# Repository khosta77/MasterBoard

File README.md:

# Мастер плата для управления ЧПУ станком

Развиваю плату.

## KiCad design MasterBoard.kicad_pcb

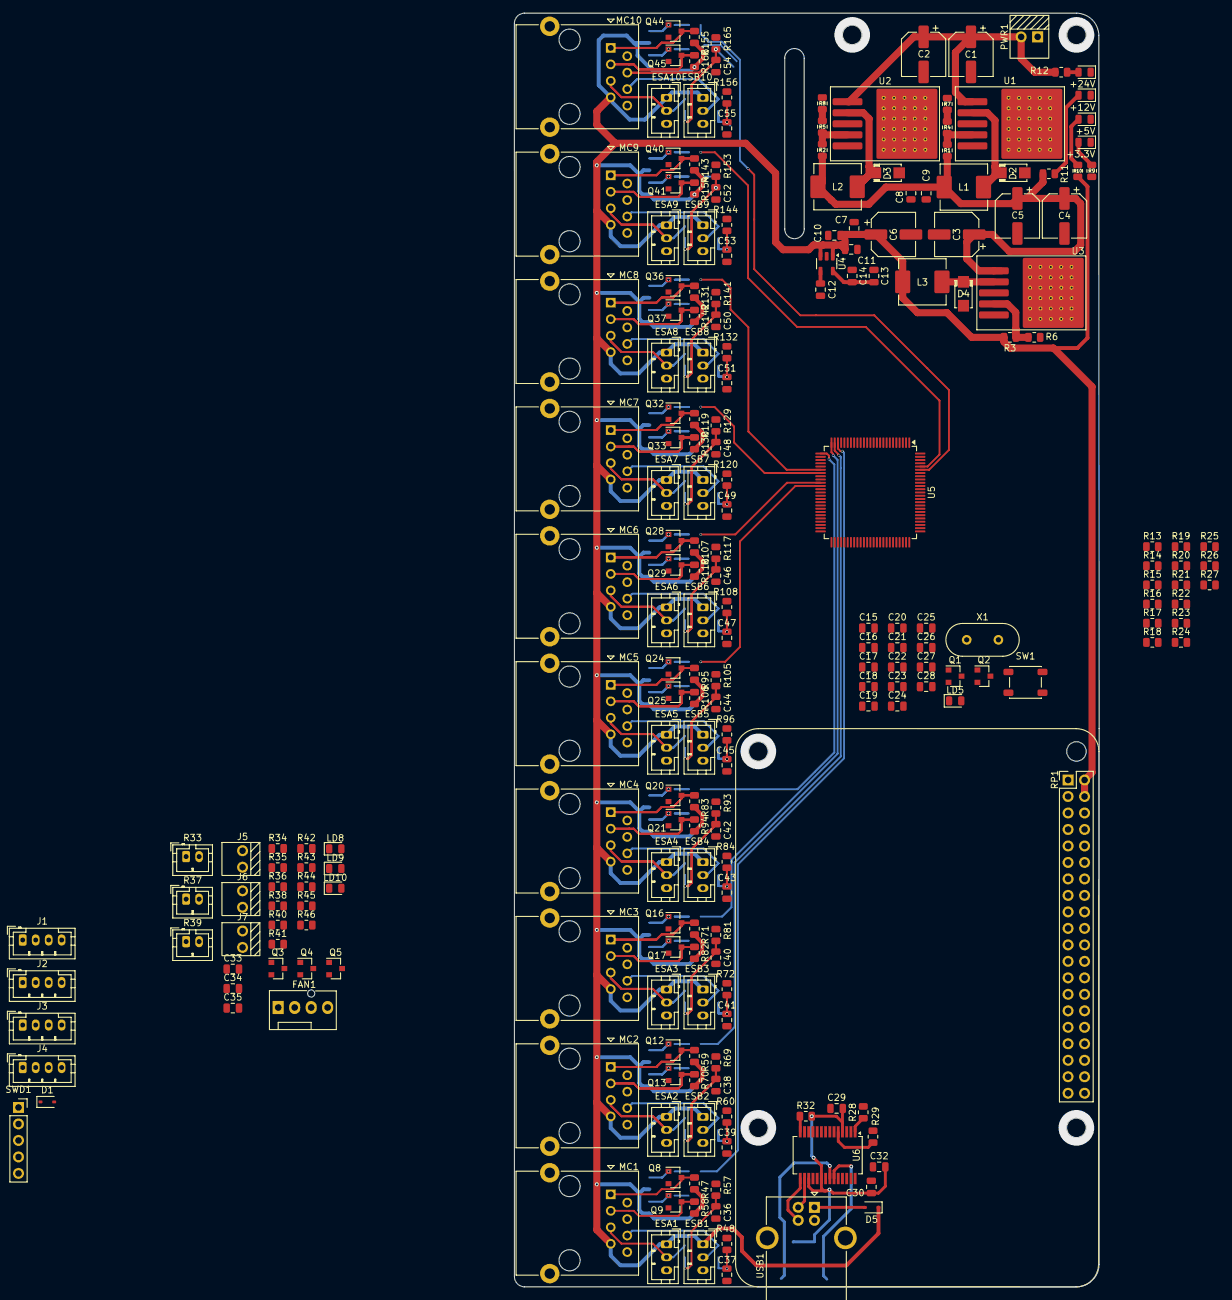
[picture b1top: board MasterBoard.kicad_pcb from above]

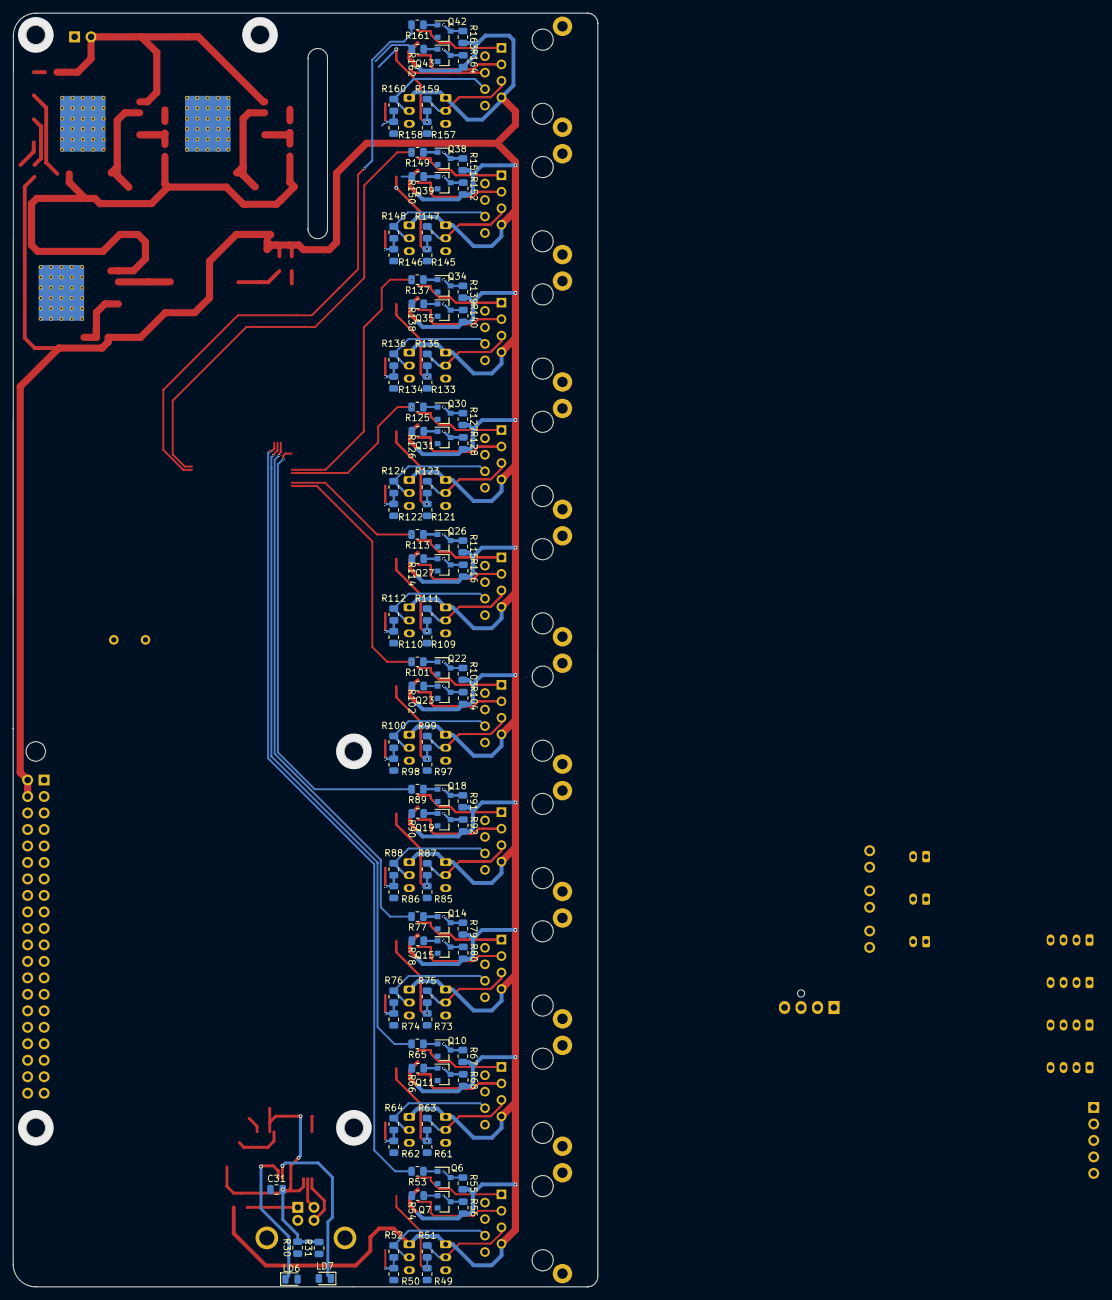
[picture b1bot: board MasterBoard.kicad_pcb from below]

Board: 2 copper layers, 90.1 x 196.2 mm, 334 parts (105 on the bottom side), 200 nets.

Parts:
C1, C2, C3: 100u; CP_Elec_6.3x7.7
C4, C5, C6: 220u; CP_Elec_6.3x7.7
C7, C8, C9: 10n; C_0805_2012Metric
C10: 1u; C_0805_2012Metric
C11, C14, C15, C18, C19, C20, C23, C24, C25, C26, C27, C30, C32, C33, C34, C35, C36, C37, C38, C39, C40, C41, C42, C43, C44, C45, C46, C47, C48, C49, C50, C51, C52, C53, C54, C55: 100n; C_0805_2012Metric
C12: 22n; C_0805_2012Metric
C13, C29: 10u; C_0805_2012Metric
C16, C17: 2.2u; C_0805_2012Metric
C21, C22: 20p; C_0805_2012Metric
C28, C31: 4.7u; C_0805_2012Metric
D1, D5: BAT60A; D_SOD-323
D2, D3, D4: 1N5822; D_DO-214AC_SMA
ESA1, ESA2, ESA3, ESA4, ESA5, ESA6, ESA7, ESA8, ESA9, ESA10: ESA; JST_PH_B3B-PH-K_1x03_P2.00mm_Vertical
ESB1, ESB2, ESB3, ESB4, ESB5, ESB6, ESB7, ESB8, ESB9, ESB10: ESB; JST_PH_B3B-PH-K_1x03_P2.00mm_Vertical
FAN1: Fan_CPU_4pin; FanPinHeader_1x04_P2.54mm_Vertical
J1, J2, J3, J4: HX711; JST_PH_B4B-PH-K_1x04_P2.00mm_Vertical
J5, J6, J7: WF-2
L1, L2, L3: 33u; L_APV_APH0650
LD1, LD2, LD3, LD4, LD5, LD6, LD7, LD8, LD9, LD10: LED_0805_2012Metric
MC1, MC2, MC3, MC4, MC5, MC6, MC7, MC8, MC9, MC10: RJ45_Shielded; RJ45_Ninigi_GE
PWR1: Conn_01x02; KLS2
Q1, Q2, Q6, Q7, Q8, Q9, Q10, Q11, Q12, Q13, Q14, Q15, Q16, Q17, Q18, Q19, Q20, Q21, Q22, Q23, Q24, Q25, Q26, Q27, Q28, Q29, Q30, Q31, Q32, Q33, Q34, Q35, Q36, Q37, Q38, Q39, Q40, Q41, Q42, Q43, Q44, Q45: MMBT3904; SOT-23
Q3, Q4, Q5: 2N7002; SOT-23
R1, R2: 1.2k; R_0805_2012Metric
R3: 3k; R_0805_2012Metric
R4, R5: 500; R_0805_2012Metric
R6, R9, R10, R11, R12, R24, R28, R29, R30, R31, R42, R44, R46: 1k; R_0805_2012Metric
R7, R8, R13, R16, R25, R26, R27, R32, R34, R38, R40, R41, R43, R45, R47, R48, R51, R52, R53, R54, R55, R56, R57, R58, R59, R60, R63, R64, R65, R66, R67, R68, R69, R70, R71, R72, R75, R76, R77, R78, R79, R80, R81, R82, R83, R84, R87, R88, R89, R90, R91, R92, R93, R94, R95, R96, R99, R100, R101, R102, R103, R104, R105, R106, R107, R108, R111, R112, R113, R114, R115, R116, R117, R118, R119, R120, R123, R124, R125, R126, R127, R128, R129, R130, R131, R132, R135, R136, R137, R138, R139, R140, R141, R142, R143, R144, R147, R148, R149, R150, R151, R152, R153, R154, R155, R156, R159, R160, R161, R162, R163, R164, R165, R166: 10k; R_0805_2012Metric
R14, R15, R17, R18, R19, R20, R21, R22, R23: 10; R_0805_2012Metric
R33, R37, R39: 10k; JST_PH_B2B-PH-K_1x02_P2.00mm_Vertical
R35, R36: -; R_0805_2012Metric
R49, R50, R61, R62, R73, R74, R85, R86, R97, R98, R109, R110, R121, R122, R133, R134, R145, R146, R157, R158: 15k; R_0805_2012Metric
RP1: Raspberry_Pi_2_3; PinHeader_2x20_P2.54mm_Vertical
SW1: SW_DPST_x2; SW_SPST_PTS647_Sx38
SWD1: Conn_01x05_Socket; PinSocket_1x05_P2.54mm_Vertical
U1, U2, U3: LM2596S-ADJ; TO-263-5_TabPin3_ThermalVias
U4: RT9193-33GB; SOT-23-5
U5: STM32F407VGTx; LQFP-100_14x14mm_P0.5mm
U6: FT232RL; SSOP-28_5.3x10.2mm_P0.65mm
USB1: USB_B; USB_B_OST_USB-B1HSxx_Horizontal
X1: 8MHz; Crystal_HC49-U_Vertical

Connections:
+3.3V: C13.2, C14.2, C18.1, C19.1, C20.1, C23.1, C24.1, C25.1, C26.1, C27.1, C28.1, C29.2, C30.2, C31.2, C32.2, C33.1, C34.1, C35.1, D1.1 (K), R9.1, R13.2, R24.2, R30.2, R31.2, R32.2, R33.1, R37.1, R39.1, R47.2, R48.2, R59.2, R60.2, R71.2, R72.2, R83.2, R84.2, R95.2, R96.2, R107.2, R108.2, R119.2, R120.2, R131.2, R132.2, R143.2, R144.2, R155.2, R156.2, RP1.1 (3V3), RP1.17 (3V3), SW1.2 (B), U4.5 (VOUT), U5.6 (VBAT), U5.11 (VDD), U5.19 (VDD), U5.21 (VREF+), U5.22 (VDDA), U5.28 (VDD), U5.50 (VDD), U5.75 (VDD), U5.100 (VDD), U6.4 (VCCIO), U6.17 (3V3OUT), U6.20 (VCC)
+5V: C6.1, C7.2, C10.2, C11.2, D5.1 (K), ESA1.1, ESA2.1, ESA3.1, ESA4.1, ESA5.1, ESA6.1, ESA7.1, ESA8.1, ESA9.1, ESA10.1, ESB1.1, ESB2.1, ESB3.1, ESB4.1, ESB5.1, ESB6.1, ESB7.1, ESB8.1, ESB9.1, ESB10.1, J1.1, J2.1, J3.1, J4.1, J5.1, J6.1, J7.1, L3.2, MC1.7, MC2.7, MC3.7, MC4.7, MC5.7, MC6.7, MC7.7, MC8.7, MC9.7, MC10.7, R3.2, R10.1, R26.2, R27.2, R55.2, R56.2, R57.2, R58.2, R67.2, R68.2, R69.2, R70.2, R79.2, R80.2, R81.2, R82.2, R91.2, R92.2, R93.2, R94.2, R103.2, R104.2, R105.2, R106.2, R115.2, R116.2, R117.2, R118.2, R127.2, R128.2, R129.2, R130.2, R139.2, R140.2, R141.2, R142.2, R151.2, R152.2, R153.2, R154.2, R163.2, R164.2, R165.2, R166.2, RP1.2 (5V), RP1.4 (5V), U4.1 (VIN), U4.3 (EN)
+12V: C3.1, C4.1, C5.1, C8.2, C9.2, FAN1.2 (+), L1.2, L2.2, R1.2, R2.2, R11.1, U3.1 (VIN)
+24V: C1.1, C2.1, PWR1.2, R12.1, U1.1 (VIN), U2.1 (VIN)
/ADC12_IN4: C33.2, R33.2, R34.1, U5.29 (PA4)
/ADC12_IN5: C34.2, R37.2, R38.1, U5.30 (PA5)
/ADC12_IN14: C35.2, R39.2, R40.1, U5.33 (PC4)
/ES_A_0: C36.1, R47.1, R49.2, R51.2
/ES_A_1: C38.1, R59.1, R61.2, R63.2
/ES_A_2: C40.1, R71.1, R73.2, R75.2
/ES_A_3: C42.1, R83.1, R85.2, R87.2
/ES_A_4: C44.1, R95.1, R97.2, R99.2
/ES_A_5: C46.1, R107.1, R109.2, R111.2
/ES_A_6: C48.1, R119.1, R121.2, R123.2
/ES_A_7: C50.1, R131.1, R133.2, R135.2
/ES_A_8: C52.1, R143.1, R145.2, R147.2
/ES_A_9: C54.1, R155.1, R157.2, R159.2
/ES_B_0: C37.1, R48.1, R50.2, R52.2
/ES_B_1: C39.1, R60.1, R62.2, R64.2
/ES_B_2: C41.1, R72.1, R74.2, R76.2
/ES_B_3: C43.1, R84.1, R86.2, R88.2
/ES_B_4: C45.1, R96.1, R98.2, R100.2
/ES_B_5: C47.1, R108.1, R110.2, R112.2
/ES_B_6: C49.1, R120.1, R122.2, R124.2
/ES_B_7: C51.1, R132.1, R134.2, R136.2
/ES_B_8: C53.1, R144.1, R146.2, R148.2
/ES_B_9: C55.1, R156.1, R158.2, R160.2
/HX711_DAT_1: J1.3, U5.82 (PD1)
/HX711_DAT_2: J2.3, U5.84 (PD3)
/HX711_DAT_3: J3.3, U5.55 (PD8)
/HX711_DAT_4: J4.3, U5.57 (PD10)
/HX711_SCK_1: J1.2, U5.81 (PD0)
/HX711_SCK_2: J2.2, U5.83 (PD2)
/HX711_SCK_3: J3.2, U5.88 (PD7)
/HX711_SCK_4: J4.2, U5.56 (PD9)
/Motor0/DIR: MC1.3, Q9.3 (C), R58.1
/Motor0/ESA: ESA1.2, MC1.5, R51.1
/Motor0/ESB: ESB1.2, MC1.6, R52.1
/Motor0/STEP: MC1.1, Q8.3 (C), R57.1
/Motor1/DIR: MC2.3, Q13.3 (C), R70.1
/Motor1/ESA: ESA2.2, MC2.5, R63.1
/Motor1/ESB: ESB2.2, MC2.6, R64.1
/Motor1/STEP: MC2.1, Q12.3 (C), R69.1
/Motor2/DIR: MC3.3, Q17.3 (C), R82.1
/Motor2/ESA: ESA3.2, MC3.5, R75.1
/Motor2/ESB: ESB3.2, MC3.6, R76.1
/Motor2/STEP: MC3.1, Q16.3 (C), R81.1
/Motor3/DIR: MC4.3, Q21.3 (C), R94.1
/Motor3/ESA: ESA4.2, MC4.5, R87.1
/Motor3/ESB: ESB4.2, MC4.6, R88.1
/Motor3/STEP: MC4.1, Q20.3 (C), R93.1
/Motor4/DIR: MC5.3, Q25.3 (C), R106.1
/Motor4/ESA: ESA5.2, MC5.5, R99.1
/Motor4/ESB: ESB5.2, MC5.6, R100.1
/Motor4/STEP: MC5.1, Q24.3 (C), R105.1
/Motor5/DIR: MC6.3, Q29.3 (C), R118.1
/Motor5/ESA: ESA6.2, MC6.5, R111.1
/Motor5/ESB: ESB6.2, MC6.6, R112.1
/Motor5/STEP: MC6.1, Q28.3 (C), R117.1
/Motor6/DIR: MC7.3, Q33.3 (C), R130.1
/Motor6/ESA: ESA7.2, MC7.5, R123.1
/Motor6/ESB: ESB7.2, MC7.6, R124.1
/Motor6/STEP: MC7.1, Q32.3 (C), R129.1
/Motor7/DIR: MC8.3, Q37.3 (C), R142.1
/Motor7/ESA: ESA8.2, MC8.5, R135.1
/Motor7/ESB: ESB8.2, MC8.6, R136.1
/Motor7/STEP: MC8.1, Q36.3 (C), R141.1
/Motor8/DIR: MC9.3, Q41.3 (C), R154.1
/Motor8/ESA: ESA9.2, MC9.5, R147.1
/Motor8/ESB: ESB9.2, MC9.6, R148.1
/Motor8/STEP: MC9.1, Q40.3 (C), R153.1
/Motor9/DIR: MC10.3, Q45.3 (C), R166.1
/Motor9/ESA: ESA10.2, MC10.5, R159.1
/Motor9/ESB: ESB10.2, MC10.6, R160.1
/Motor9/STEP: MC10.1, Q44.3 (C), R165.1
/RP_RST: C15.1, R13.1, RP1.12 (GPIO18/PWM0), SW1.1 (A), U5.14 (NRST)
/RP_UART1_RX: R14.2, RP1.28 (ID_SC/GPIO1)
/RP_UART1_TX: R15.2, RP1.27 (ID_SD/GPIO0)
/RP_UART_RX: R17.1, RP1.10 (GPIO15/RXD)
/RP_UART_TX: R18.1, RP1.8 (GPIO14/TXD)
/SOME_PIN_0: RP1.22 (GPIO25), U5.7 (PC13)
/SOME_PIN_1: RP1.37 (GPIO26), U5.8 (PC14)
/SOME_PIN_2: RP1.13 (GPIO27), U5.9 (PC15)
/SPI2_CS: R19.1, RP1.24 (~CE0/GPIO8)
/SPI2_MISO: R22.1, RP1.21 (MISO0/GPIO9)
/SPI2_MOSI: R23.1, RP1.19 (MOSI0/GPIO10)
/SPI2_NSS: R20.1, RP1.26 (~CE1/GPIO7)
/SPI2_SCK: R21.1, RP1.23 (SCLK0/GPIO11)
/STM32F407VG/OSC_IN: C21.2, U5.12 (PH0), X1.2
/STM32F407VG/OSC_OUT: C22.2, U5.13 (PH1), X1.1
/STM32F407VG/PA8: LD5.1 (K), U5.67 (PA8)
/STM32F407VG/PD4: R25.2, U5.85 (PD4)
/SWCLK: SWD1.3, U5.76 (PA14)
/SWDIO: SWD1.2, U5.72 (PA13)
/TIM2/5_STEP_1: R53.2, U5.23 (PA0)
/TIM2/5_STEP_2: R65.2, U5.24 (PA1)
/TIM2/5_STEP_3: R77.2, U5.25 (PA2)
/TIM2/5_STEP_4: R89.2, U5.26 (PA3)
/TIM3_STEP_1: R137.2, U5.31 (PA6)
/TIM3_STEP_2: R125.2, U5.32 (PA7)
/TIM3_STEP_3: R113.2, U5.35 (PB0)
/TIM3_STEP_4: R101.2, U5.36 (PB1)
/TIM4_PWM_3: Q3.1 (G), R41.2, U5.93 (PB7)
/TIM4_PWM_4: Q5.1 (G), R45.2, U5.92 (PB6)
/TIM4_STEP_1: R149.2, U5.96 (PB9)
/TIM4_STEP_2: R161.2, U5.95 (PB8)
/TIM8_2_TABLE_ON: Q4.1 (G), R43.2, U5.64 (PC7)
/TIM8_3_FAN_PWM: FAN1.4 (PWM), U5.65 (PC8)
/TIM8_4_TACHO: R35.1, R36.2, U5.66 (PC9)
EN: MC1.4, MC2.4, MC3.4, MC4.4, MC5.4, MC6.4, MC7.4, MC8.4, MC9.4, MC10.4, Q2.3 (C), R27.1
GND: C1.2, C2.2, C3.2, C4.2, C5.2, C6.2, C7.1, C8.1, C9.1, C10.1, C11.1, C12.1, C13.1, C14.1, C15.2, C16.2, C17.2, C18.2, C19.2, C20.2, C21.1, C22.1, C23.2, C24.2, C25.2, C26.2, C27.2, C28.2, C29.1, C30.1, C31.1, C32.1, C36.2, C37.2, C38.2, C39.2, C40.2, C41.2, C42.2, C43.2, C44.2, C45.2, C46.2, C47.2, C48.2, C49.2, C50.2, C51.2, C52.2, C53.2, C54.2, C55.2, D2.2 (A), D3.2 (A), D4.2 (A), ESA1.3, ESA2.3, ESA3.3, ESA4.3, ESA5.3, ESA6.3, ESA7.3, ESA8.3, ESA9.3, ESA10.3, ESB1.3, ESB2.3, ESB3.3, ESB4.3, ESB5.3, ESB6.3, ESB7.3, ESB8.3, ESB9.3, ESB10.3, FAN1.1 (-), J1.4, J2.4, J3.4, J4.4, LD1.1 (K), LD2.1 (K), LD3.1 (K), LD4.1 (K), MC1.2, MC1.8, MC1.SH, MC2.2, MC2.8, MC2.SH, MC3.2, MC3.8, MC3.SH, MC4.2, MC4.8, MC4.SH, MC5.2, MC5.8, MC5.SH, MC6.2, MC6.8, MC6.SH, MC7.2, MC7.8, MC7.SH, MC8.2, MC8.8, MC8.SH, MC9.2, MC9.8, MC9.SH, MC10.2, MC10.8, MC10.SH, PWR1.1, Q1.2 (E), Q2.2 (E), Q3.2 (S), Q4.2 (S), Q5.2 (S), Q6.2 (E), Q7.2 (E), Q8.2 (E), Q9.2 (E), Q10.2 (E), Q11.2 (E), Q12.2 (E), Q13.2 (E), Q14.2 (E), Q15.2 (E), Q16.2 (E), Q17.2 (E), Q18.2 (E), Q19.2 (E), Q20.2 (E), Q21.2 (E), Q22.2 (E), Q23.2 (E), Q24.2 (E), Q25.2 (E), Q26.2 (E), Q27.2 (E), Q28.2 (E), Q29.2 (E), Q30.2 (E), Q31.2 (E), Q32.2 (E), Q33.2 (E), Q34.2 (E), Q35.2 (E), Q36.2 (E), Q37.2 (E), Q38.2 (E), Q39.2 (E), Q40.2 (E), Q41.2 (E), Q42.2 (E), Q43.2 (E), Q44.2 (E), Q45.2 (E), R6.2, R7.2, R8.2, R16.2, R34.2, R36.1, R38.2, R40.2, R41.1, R43.1, R45.1, R49.1, R50.1, R61.1, R62.1, R73.1, R74.1, R85.1, R86.1, R97.1, R98.1, R109.1, R110.1, R121.1, R122.1, R133.1, R134.1, R145.1, R146.1, R157.1, R158.1, RP1.6 (GND), RP1.9 (GND), RP1.11 (GPIO17), RP1.14 (GND), RP1.20 (GND), RP1.25 (GND), RP1.30 (GND), RP1.34 (GND), RP1.39 (GND), SWD1.4, U1.3 (GND), U1.5 (~ON/OFF), U2.3 (GND), U2.5 (~ON/OFF), U3.3 (GND), U3.5 (~ON/OFF), U4.2 (GND), U5.10 (VSS), U5.20 (VSSA), U5.27 (VSS), U5.74 (VSS), U5.99 (VSS), U6.7 (GND), U6.18 (GND), U6.21 (GND), U6.25 (AGND), U6.26 (TEST), USB1.4 (GND), USB1.5 (Shield)
unnamed: D1.2 (A), SWD1.1
unnamed: D2.1 (K), L1.1, U1.2 (OUT)
unnamed: D3.1 (K), L2.1, U2.2 (OUT)
unnamed: D4.1 (K), L3.1, U3.2 (OUT)
unnamed: D5.2 (A), USB1.1 (VBUS)
unnamed: FAN1.3 (Tacho), R35.2
unnamed: J5.2, LD8.2 (A)
unnamed: J6.2, LD9.2 (A)
unnamed: J7.2, LD10.2 (A)
unnamed: LD1.2 (A), R9.2
unnamed: LD2.2 (A), R10.2
unnamed: LD3.2 (A), R11.2
unnamed: LD4.2 (A), R12.2
unnamed: LD5.2 (A), R24.1
unnamed: LD6.2 (A), R30.1
unnamed: LD6.1 (K), U6.23 (CBUS0)
unnamed: LD7.2 (A), R31.1
unnamed: LD7.1 (K), U6.22 (CBUS1)
unnamed: LD8.1 (K), R42.1
unnamed: LD9.1 (K), R44.1
unnamed: LD10.1 (K), R46.1
unnamed: Q1.1 (B), R25.1
unnamed: Q1.3 (C), Q2.1 (B), R26.1
unnamed: Q3.3 (D), R42.2
unnamed: Q4.3 (D), R44.2
unnamed: Q5.3 (D), R46.2
unnamed: Q6.1 (B), R53.1
unnamed: Q6.3 (C), Q8.1 (B), R55.1
unnamed: Q7.1 (B), R54.1
unnamed: Q7.3 (C), Q9.1 (B), R56.1
unnamed: Q10.1 (B), R65.1
unnamed: Q10.3 (C), Q12.1 (B), R67.1
unnamed: Q11.1 (B), R66.1
unnamed: Q11.3 (C), Q13.1 (B), R68.1
unnamed: Q14.1 (B), R77.1
unnamed: Q14.3 (C), Q16.1 (B), R79.1
unnamed: Q15.1 (B), R78.1
unnamed: Q15.3 (C), Q17.1 (B), R80.1
unnamed: Q18.1 (B), R89.1
unnamed: Q18.3 (C), Q20.1 (B), R91.1
unnamed: Q19.1 (B), R90.1
unnamed: Q19.3 (C), Q21.1 (B), R92.1
unnamed: Q22.1 (B), R101.1
unnamed: Q22.3 (C), Q24.1 (B), R103.1
unnamed: Q23.1 (B), R102.1
unnamed: Q23.3 (C), Q25.1 (B), R104.1
unnamed: Q26.1 (B), R113.1
unnamed: Q26.3 (C), Q28.1 (B), R115.1
unnamed: Q27.1 (B), R114.1
unnamed: Q27.3 (C), Q29.1 (B), R116.1
unnamed: Q30.1 (B), R125.1
unnamed: Q30.3 (C), Q32.1 (B), R127.1
unnamed: Q31.1 (B), R126.1
unnamed: Q31.3 (C), Q33.1 (B), R128.1
unnamed: Q34.1 (B), R137.1
unnamed: Q34.3 (C), Q36.1 (B), R139.1
unnamed: Q35.1 (B), R138.1
unnamed: Q35.3 (C), Q37.1 (B), R140.1
unnamed: Q38.1 (B), R149.1
unnamed: Q38.3 (C), Q40.1 (B), R151.1
unnamed: Q39.1 (B), R150.1
unnamed: Q39.3 (C), Q41.1 (B), R152.1
unnamed: Q42.1 (B), R161.1
unnamed: Q42.3 (C), Q44.1 (B), R163.1
unnamed: Q43.1 (B), R162.1
unnamed: Q43.3 (C), Q45.1 (B), R164.1
unnamed: R4.2, R7.1
unnamed: R5.2, R8.1
unnamed: R1.1, R4.1, U1.4 (FB)
unnamed: R2.1, R5.1, U2.4 (FB)
unnamed: R3.1, R6.1, U3.4 (FB)
unnamed: C12.2, U4.4 (BP)
unnamed: R16.1, U5.94 (BOOT0)
unnamed: R17.2, U5.68 (PA9)
unnamed: R18.2, U5.69 (PA10)
unnamed: R19.2, U5.48 (PB11)
unnamed: R20.2, U5.51 (PB12)
unnamed: R21.2, U5.52 (PB13)
unnamed: R22.2, U5.53 (PB14)
unnamed: R23.2, U5.54 (PB15)
unnamed: R14.1, U5.86 (PD5)
unnamed: R15.1, U5.87 (PD6)
unnamed: C16.1, U5.49 (VCAP_1)
unnamed: C17.1, U5.73 (VCAP_2)
unnamed: R32.1, U6.14 (CBUS3)
unnamed: R29.1, U6.5 (RXD)
unnamed: R28.1, U6.1 (TXD)
unnamed: U6.15 (USBD+), USB1.3 (D+)
unnamed: U6.16 (USBD-), USB1.2 (D-)

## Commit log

2025-02-22 Искл файлы
2025-02-22 Файлы проекта
2025-02-22 Схемы stm32f4, stlink финальные, в power еще что нибудь добавлю. Остальные пока не подключены
2025-02-24 Еще одно искл
2025-02-24 Обновил файлы и добавил новые элемнты
2025-02-24 Внутренние изменения
2025-02-25 Новые схемы, множество
2025-02-25 Добавил много схем, близок к тому чтобы общий вид платы доделать
2025-02-27 Добавил концевик в схему и подправил схему мотора
2025-02-27 Добавил движки, концевики, и шлейфы
2025-02-27 Модуль W5500
2025-02-27 Добавил модуль W5500. Посчитал амбиции платы, не хватает пинов в МК, решил удалить(убрать из симуляции) концевики дополнительные
2025-03-01 Что-то поменялось
2025-03-01 Добавил еще один интернет модуль
2025-03-01 Добавил карту памяти
2025-03-01 Поменял микроконтроллер на поменьше
2025-03-01 Файлы измененный Kicad
2025-03-01 Начал править нумерацию элементов, и устанавливать посадочные места
2025-03-01 Прошелся по всей схеме: 1. почистил компоненты; 2. задал посадочные места; 3. Выставил все ссылки на плате в притык, дальнейшее расширение - смена мк
2025-03-01 Часть с схемой платы в кокойто степени дошла до этапа дебага
2025-03-01 Хмм в библиотеки был косяк
2025-03-01 Выгрузил элементы в трассировщик, модели все подгружены, настал этап трассировки платы
2025-03-04 Не корректно посадочное место выбрал
2025-03-04 Радикальное рубилово частей схемы
2025-03-04 Решил отказатся от платы Ender
2025-03-05 Перенс файлы что надо бы сохранить на всякий в отдельную директорию
2025-03-05 Множественные модификации
2025-03-05 Обновил плату, убрал много элементов. посчитал, что так будет лучше
2025-03-06 Надо будет сохранить
2025-03-06 Сохранил буфер
2025-03-06 Добавил описание и лицензию
2025-03-12 Был косяк в обозначениях
2025-03-12 Начал делать трассировку
2025-03-12 Новое исключение
2025-03-14 Изменил на подключение промышленного мотора
2025-03-14 Удалил TMP100 - лишний груз был
2025-03-14 Обновил/почистил схему
2025-03-14 Мелкие перестановки, просто кое что прикидывал
2025-03-14 Вернул старый добрый микроконтроллер
2025-03-14 Вынес перефирию в отдельный блок, в данный момент так разумнее
2025-03-14 Предфинальный облик мотора, нужно еще добавить пару моментов
2025-03-14 Множественная перекомпоновка
2025-03-14 Системные измененния
2025-03-14 Удалил уже не используемые файлы
2025-03-14 Добавил разъемы, для концевиков
2025-03-14 Добавил кнопку на сброс
2025-03-14 Вывел все выводы, но еще не соединил
2025-03-14 Выписал из схемы какого то препода, которого не понятно за чем вписал....
2025-03-18 Множественные обновления схем
2025-03-18 Придумал название для данного поколения
2025-03-18 Обновил обозначения, а то старая нумерация была специфической
2025-03-18 Было еще что-то 1206
2025-03-18 Начал трассировать плату
2025-03-19 Начал радиакально трассировать плату, вывел все порты для шаговиков
2025-03-20 Правки схем, возможно что-то было не корректно выбрано
2025-03-20 Правки подключения, чтобы удобнее было трассировать
2025-03-20 Этап трассировки полным ходом
2025-03-20 Переподключения, для оптимальной трассировки
2025-03-20 Оптимизировал схему для трассировки
2025-03-20 Плата польностью трассирована
2025-03-20 Крупная веха в разработке завершена, передаю на ревью
2025-03-20 Последнее обновление
2025-03-20 Файлы для производства
2025-03-21 Изменил список авторов
2025-03-21 Мелкие правки схемы
2025-03-21 Крутил, смотрел схему
2025-03-28 Ревью затянулось
